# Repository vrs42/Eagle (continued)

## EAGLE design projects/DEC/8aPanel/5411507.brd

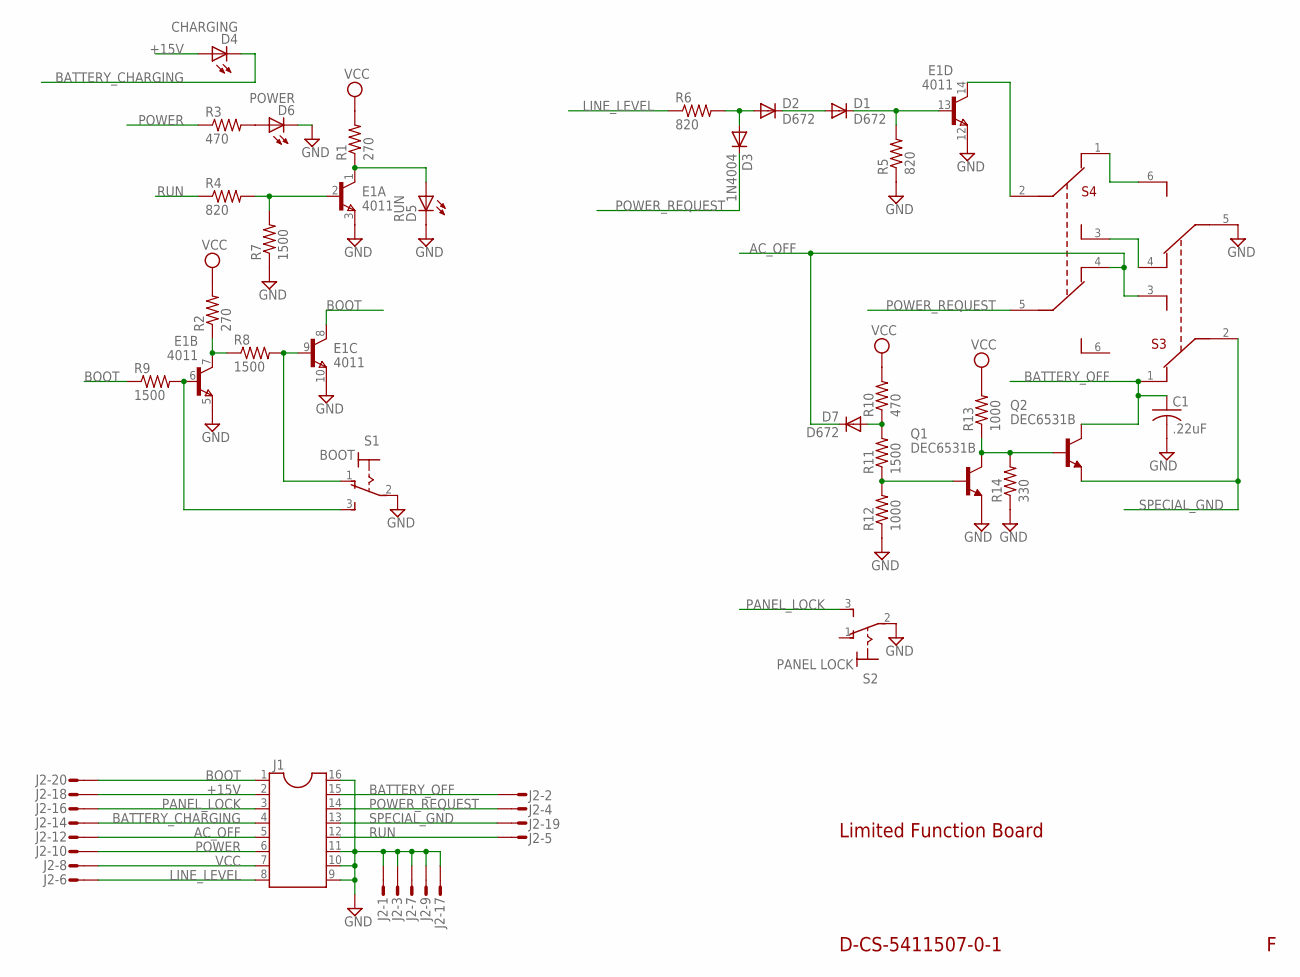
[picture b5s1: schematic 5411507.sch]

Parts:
C1: .22uF; C050-030X075
D1, D2, D7: D672; DO35-10
D3: 1N4004; DO41-10
D4: CHARGING; LED5MM
D5: RUN; LED5MM
D6: POWER; LED5MM
E1: 4011; DIL14
J1: SOCKET-16
J2: 20H
Q1, Q2: DEC6531B; TO5
R1, R2: 270; 0207/10
R3, R10: 470; 0207/10
R4, R5, R6: 820; 0207/10
R7, R8, R9, R11: 1500; 0207/10
R12, R13: 1000; 0207/10
R14: 330; 0207/10
S1: BOOT; 7109MD9V3
S2: PANEL LOCK; 7109MD9V3
S3: ON/OFF; 7209MD9V3
S4: M/S; 7209MD9V3

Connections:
+15V: D4.A, J1.2, J2.18
AC_OFF: D7.C, J1.5, J2.12, S3.3 (A3), S4.4 (B1)
BATTERY_CHARGING: D4.K (C), J1.4, J2.14
BATTERY_OFF: C1.1, J1.15, J2.2, Q2.3 (C), S3.1 (A1)
BOOT: E1.8 (C), J1.1, J2.20, R9.1
GND: C1.2, D5.K (C), D6.K (C), E1.3 (E), E1.5 (E), E1.10 (E), E1.12 (E), J1.9, J1.10, J1.11, J1.16, J2.1, J2.3, J2.7, J2.9, J2.17, Q1.1 (E), R5.1, R7.1, R12.1, R14.1, S1.2, S1.NC@1 (GND), S1.NC@2 (GND), S1.NC@3 (GND), S1.NC@4 (GND), S1.NC@5 (GND), S1.NC@6 (GND), S1.NC@7 (GND), S1.NC@8 (GND), S2.2, S2.NC@1 (GND), S2.NC@2 (GND), S2.NC@3 (GND), S2.NC@4 (GND), S2.NC@5 (GND), S2.NC@6 (GND), S2.NC@7 (GND), S2.NC@8 (GND), S3.5 (B2), S3.NC@1 (GND), S3.NC@2 (GND), S3.NC@3 (GND), S3.NC@4 (GND), S3.NC@5 (GND), S3.NC@6 (GND), S3.NC@7 (GND), S3.NC@8 (GND), S4.NC@1 (GND), S4.NC@2 (GND), S4.NC@3 (GND), S4.NC@4 (GND), S4.NC@5 (GND), S4.NC@6 (GND), S4.NC@7 (GND), S4.NC@8 (GND)
LINE_LEVEL: J1.8, J2.6, R6.1
unnamed: D6.A, R3.2
unnamed: Q1.3 (C), Q2.2 (B), R13.1, R14.2
unnamed: D7.A, R10.1, R11.2
unnamed: Q1.2 (B), R11.1, R12.2
unnamed: D1.A, D2.C
unnamed: D1.C, E1.13 (B), R5.2
unnamed: S3.4 (B1), S4.3 (A3)
unnamed: S3.6 (B3), S4.1 (A1)
unnamed: D2.A, D3.A, R6.2
unnamed: E1.2 (B), R4.2, R7.2
unnamed: D5.A, E1.1 (C), R1.1
unnamed: E1.7 (C), R2.1, R8.1
unnamed: E1.6 (B), R9.2, S1.3 (S)
unnamed: E1.9 (B), R8.2, S1.1 (O)
unnamed: E1.14 (C), S4.2 (A2)
PANEL_LOCK: J1.3, J2.16, S2.3 (S)
POWER: J1.6, J2.10, R3.1
POWER_REQUEST: D3.C, J1.14, J2.4, S4.5 (B2)
RUN: J1.12, J2.5, R4.1
SPECIAL_GND: J1.13, J2.19, Q2.1 (E), S3.2 (A2)
VCC: J1.7, J2.8, R1.2, R2.2, R10.2, R13.2

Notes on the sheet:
D-CS-5411507-0-1
Limited Function Board

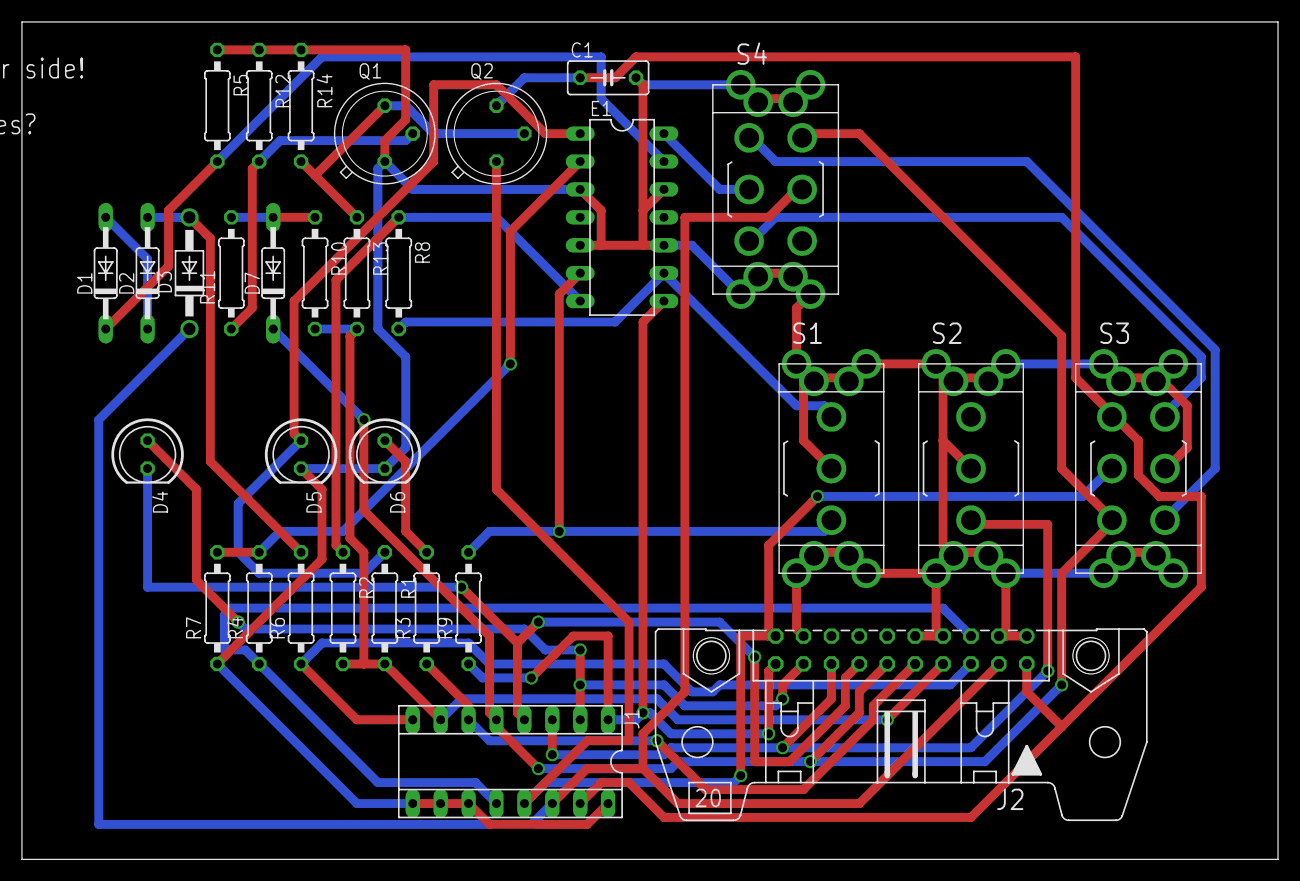
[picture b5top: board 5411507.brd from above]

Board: 2 copper layers, 114.3 x 76.2 mm, 31 parts (0 on the bottom side), 28 nets.
